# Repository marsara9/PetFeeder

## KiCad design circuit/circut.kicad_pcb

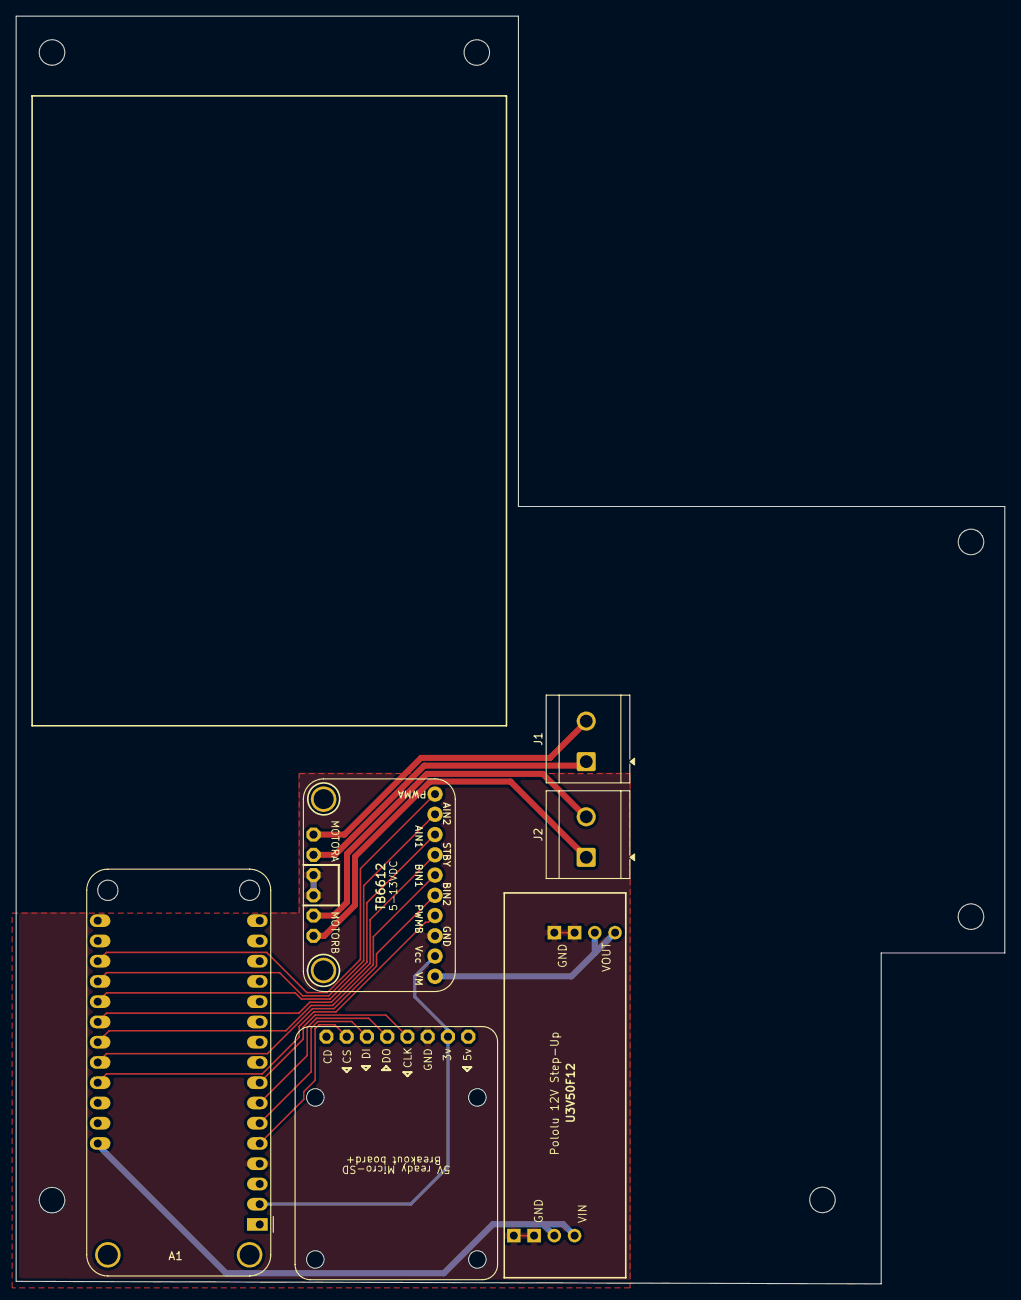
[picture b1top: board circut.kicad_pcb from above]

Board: 2 copper layers, 124.0 x 159.0 mm, 6 parts (0 on the bottom side), 19 nets.

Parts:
A1: Adafruit_Feather_HUZZAH32_ESP32; Adafruit_Feather_WithMountingHoles
J1, J2: Screw_Terminal_01x02; TerminalBlock_CUI_TB007-508-02_1x02_P5.08mm_Horizontal
J3: Conn_02x04_Top_Bottom; Pololu 12v StepUp
SD1: Conn_01x08; Adafruit Micro-SD Breakout
U1: TB6612FNG; Adafruit TB6612

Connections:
/3v: A1.2 (3V3), SD1.2, U1.20 (VCC)
/12v: J3.7, J3.8, U1.24 (VM1)
/AIN1: A1.21 (A8/IO15), U1.21 (AIN1)
/AIN2: A1.20 (A7/IO32), U1.22 (AIN2)
/BIN1: A1.23 (A10/IO27), U1.17 (BIN1)
/BIN2: A1.24 (A11/IO12), U1.16 (BIN2)
/Battery: A1.28 (VBAT), J3.3, J3.4
/PWMA: A1.19 (A6/IO14), U1.23 (PWMA)
/PWMB: A1.25 (A12/IO13), U1.15 (PWMB)
/STBY: A1.22 (A9/IO33), U1.19 (STBY)
GND: A1.4 (GND), J3.1, J3.2, J3.5, J3.6, SD1.3, U1.3 (PGND1), U1.9 (PGND2), U1.18 (GND)
unnamed: A1.6 (DAC1/A1), SD1.6
unnamed: A1.5 (DAC2/A0), SD1.7
unnamed: A1.7 (I34/A2), SD1.5
unnamed: A1.8 (I39/A3), SD1.4
unnamed: J1.1, U1.1 (AO1)
unnamed: J1.2, U1.5 (AO2)
unnamed: J2.1, U1.11 (BO1)
unnamed: J2.2, U1.7 (BO2)

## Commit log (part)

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2020-07-21 adding code to develop
2020-07-21 adding 3d prints and circuit designs
2020-07-21 Adding Postmain API file
2020-07-21 Adding sketchup design.
2020-07-21 adding generic functions for reading and writing raw data to the SD card.
2020-07-21 adding reading/writing Feedings and Schedules
2020-07-21 updating stl files
2020-07-21 fixing memory leak
2020-07-22 renaming ActivityHistory to DataStore; implementing more of the methods.
2020-07-22 updating sketch
2020-07-22 Fixing MDNS
2020-07-22 Removing support to store data in EEPROM if SD card is not available. An SD card is now required. Added support for storing Settings.
2020-07-22 replacing char* with std::string for easier memory management.
2020-07-22 fixed SD card implementaion
2020-07-23 - Fixing memory leaks with DataStore - Fixing issue with mDNS not working - If no name is set, a random name is generated and used instead. This same name is ALWAYS used as the access point name when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
2020-07-25 Fixing issue with stepper motor causing watchdog reset.
2020-07-25 Implementing GET /feed to get all of the feedings.
2020-07-25 fixing headers.
2020-07-25 code cleanup
2020-07-26 Adding scheduler
2020-07-26 Adding GET/POST requests to get or add new scheduled feedings.
2020-07-26 Fixed bug with DataStore::writeBytesToFile Adding logging for any web server requests
2020-07-26 implementing scheduleToJson
2020-07-26 Fixed issue with DataStore crashing Implemented POST / GET `/schedule`.
2020-07-26 fixing bug in time calculation. fixing bug where the feeder would dispense at boot.
2020-07-26 updating postman api
2020-07-26 Implementing DELETE settings to restore factory default settings.
2020-07-27 Initial checkin for Android app.
2020-07-27 Adding ViewModels setting up project structure.
2020-07-27 Adding Retrofit and RxKotlin
2020-07-28 Starting work on settings screen
2020-07-28 Exposing Binding from ViewDataBinding to be used later.
2020-07-28 Continuing work on Settings
2020-07-28 cleaning up imports
2020-07-28 Cleaning up dialogs
2020-07-28 Moving settings module to the settings package
2020-07-28 Adding schedules fragment.
2020-07-28 Adding History service calls and view models.
2020-07-28 Fixing issue with settings not reloading correctly. Adding option to reset to factory defaults.
2020-07-29 Updating launcher icon
2020-07-29 Adding DashboardViewModel
2020-07-29 Adding UUID generator Schedule now works with bytes instead of ints Fixed feeding's JSON to emit 'date' instead of 'time'.
2020-07-29 Dashboard now launches on startup
2020-07-29 Adding FCM libraries.
2020-07-29 Adding HistoryFragment. Code cleanup.
2020-07-29 Adding FCM token to Settings screen
2020-07-29 continuing work on FCM service
2020-07-29 working on notification server implementation on feeder.
2020-07-29 moving android notification logic to its own method
2020-07-30 Fixing notification server.
2020-07-30 the FCM SHA Footprint can now be updated via /settings
2020-07-30 code cleanup.
2020-07-30 updating Android to be able to set the FCM fingerprint via /setttings
2020-07-30 Adding repositories to manager your current feeder.
2020-07-30 standardizing mDNS name to PetFeeder and implementing NSD on Android.
2020-07-30 Fixing memory leak with ViewModels and Rx.
2020-07-31 Adding option to launch setup screen
2020-07-31 Begining work on setup screen.
2020-07-31 Adding service call to delete a scheduled feeding
2020-08-03 Fixing NSD implementation. Starting work on first setup screen.
2020-08-03 continuing to fix mDNS implementation
2020-08-04 Adding build_file_checksums to gitignore
2020-08-04 adding classes to be used for each step along the way.
2020-08-05 Refactoring setup to use Fragments
2020-08-05 Adding new setup fragments.
2020-08-06 continuing work on setup screen.
2020-08-06 more work on setup
2020-08-10 Refactoring Setup once again, Finally got it ths time.
2020-08-12 Working on scanning step for setup.
2020-08-19 updating to ArduinoJson 6
2020-08-20 Adding history fragment layout and hooking up bindings.
2020-08-20 Fixing an issue where the scheduler wasn't adding a new scheduled event correctly after the first one finished.
2020-08-20 Unifiying section header design
2020-08-20 Finally fixed the scheduler.
2020-08-25 Disabling stepper to conserve power when not in use.
2020-08-25 History tab now shows time of feeding.
2020-11-18 refactored actrion bar
2020-11-18 fixed synchronization issue
2020-11-18 update project
2020-11-19 Adding avatar image Fixing sort order of feeders in drop down.
2020-11-19 Sorting history from newest to oldest.
2020-11-19 designing scheduling screen and viewModel.
2020-11-20 adding more icons for time of day when scheduling a feeding.
2020-11-20 updating funnel design to hopefully not get trapped food as much
2020-11-20 Adding Dialog for adding a new scheduled feeding (wip)
2020-11-20 Updating feeder firmware to support esp32.
2020-11-25 Testing material design TimePickerDialog
2020-11-27 Updating add scheduled feeding dialog.
2020-12-02 Updating feeder design to use an auger instead of a turn table.
2020-12-07 update feeder design
2021-11-16 Editing feeder design so that motor screws can be recessed Fixing typo in notifications.h
2022-01-07 Updating libraries to new versions.
2022-01-31 Fixing build issues after upgrading to ArcticFox
2022-05-24 Updating app app to API 32 and support for Android Studio Chipmunk
2022-06-06 cleaning up warnings
2022-06-07 Migrating from RxJava to Kotlin Coroutines.
2022-06-10 Fixing bug with updating StateFlows
